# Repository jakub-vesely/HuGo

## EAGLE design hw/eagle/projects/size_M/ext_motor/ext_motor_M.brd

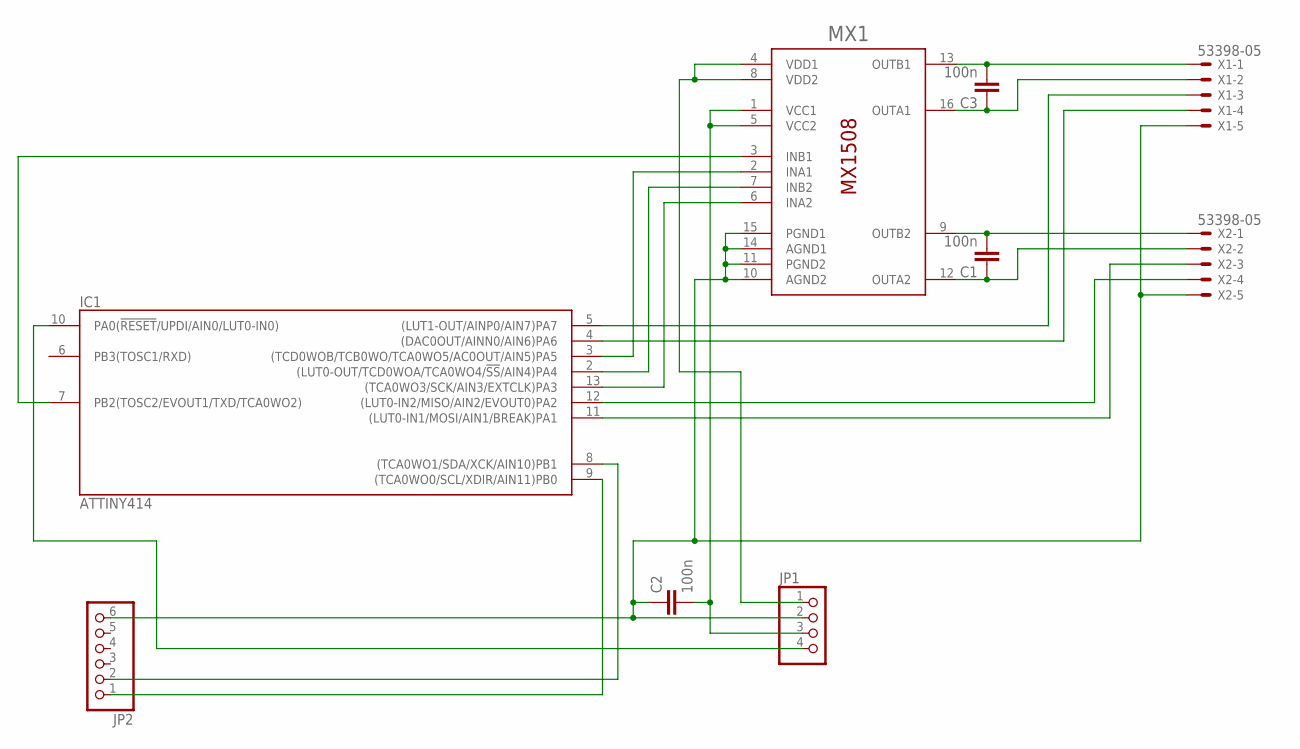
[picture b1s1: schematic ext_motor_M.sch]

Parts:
C1, C2, C3: 100n; C0805K
IC1: ATTINY414; SO14
JP1: PINHD-1X4; 1X04
JP2: PINHD-1X6; 1X06
MX1: MX1508; SOP16
X1, X2: 53398-05

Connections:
FOTO1: IC1.5 ((LUT1-OUT/AINP0/AIN7)PA7), X1.3
FOTO2: IC1.12 ((LUT0-IN2/MISO/AIN2/EVOUT0)PA2), X2.4
GND: C2.1, IC1.14 (GND), JP1.2, JP2.6, MX1.10 (AGND2), MX1.11 (PGND2), MX1.14 (AGND1), MX1.15 (PGND1), X1.5, X2.5
INA1: IC1.3 ((TCD0WOB/TCB0WO/TCA0WO5/AC0OUT/AIN5)PA5), MX1.2 (INA1)
INA2: IC1.13 ((TCA0WO3/SCK/AIN3/EXTCLK)PA3), MX1.6 (INA2)
INB1: IC1.7 (PB2(TOSC2/EVOUT1/TXD/TCA0WO2)), MX1.3 (INB1)
INB2: IC1.2 ((LUT0-OUT/TCD0WOA/TCA0WO4/!SS!/AIN4)PA4), MX1.7 (INB2)
LED1: IC1.4 ((DAC0OUT/AINN0/AIN6)PA6), X1.4
LED2: IC1.11 ((LUT0-IN1/MOSI/AIN1/BREAK)PA1), X2.3
M1: C3.2, MX1.13 (OUTB1), X1.1
M2: C3.1, MX1.16 (OUTA1), X1.2
M3: C1.2, MX1.9 (OUTB2), X2.1
M4: C1.1, MX1.12 (OUTA2), X2.2
M_SRC: JP1.1, MX1.4 (VDD1), MX1.8 (VDD2)
unnamed: IC1.10 (PA0(!RESET!/UPDI/AIN0/LUT0-IN0)), JP1.4
unnamed: IC1.9 ((TCA0WO0/SCL/XDIR/AIN11)PB0), JP2.1
unnamed: IC1.8 ((TCA0WO1/SDA/XCK/AIN10)PB1), JP2.2
VCC: C2.2, IC1.1 (VCC), JP1.3, MX1.1 (VCC1), MX1.5 (VCC2)

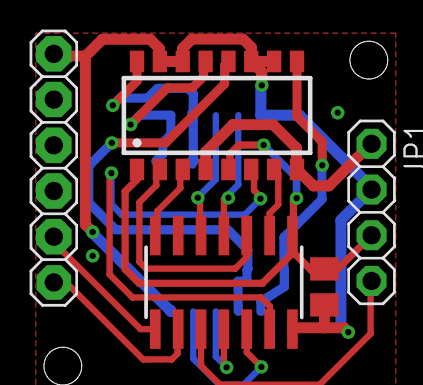
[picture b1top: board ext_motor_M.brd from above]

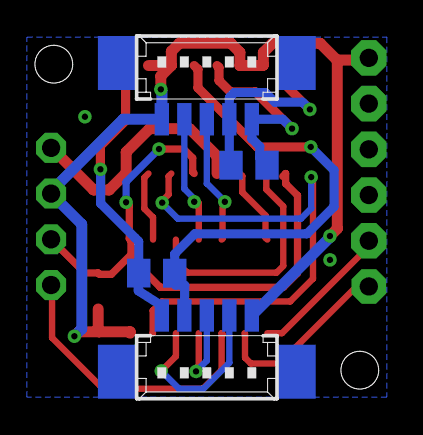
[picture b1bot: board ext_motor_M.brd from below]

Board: 2 copper layers, 9 parts (4 on the bottom side), 18 nets.

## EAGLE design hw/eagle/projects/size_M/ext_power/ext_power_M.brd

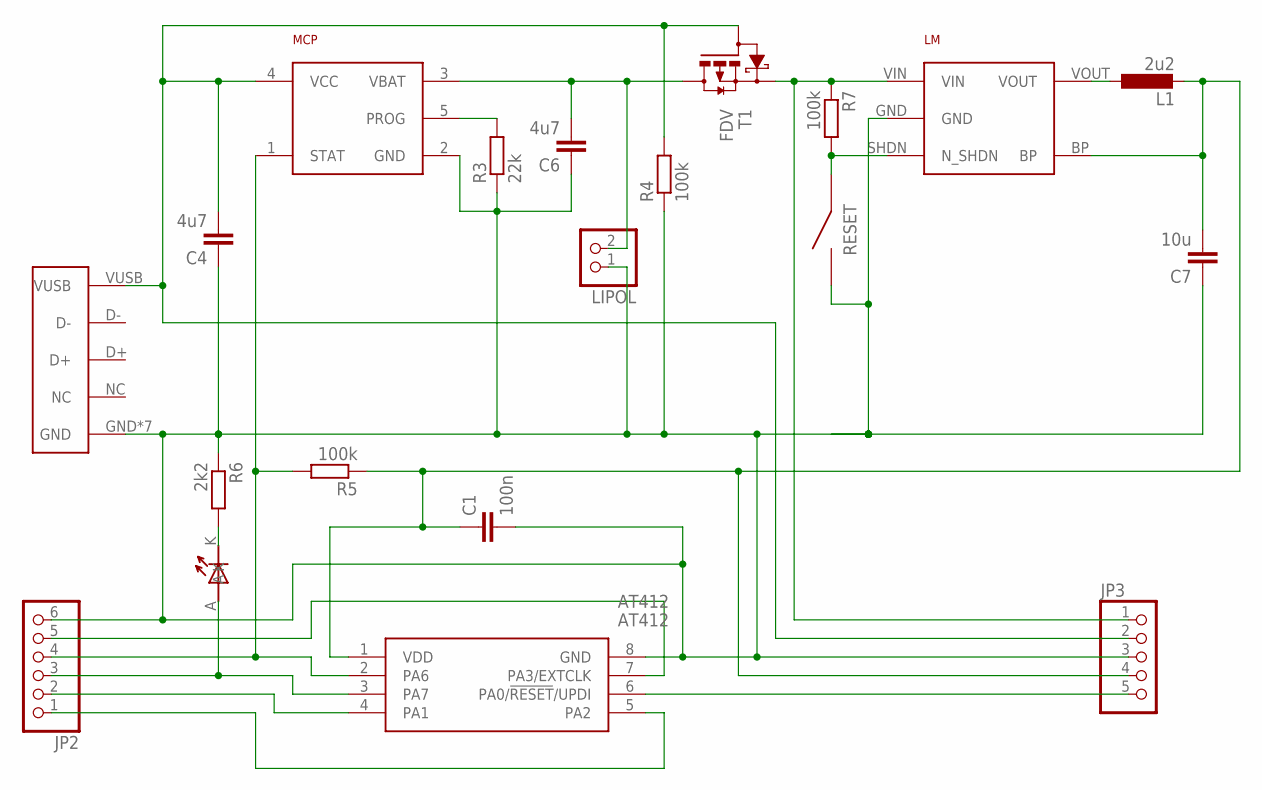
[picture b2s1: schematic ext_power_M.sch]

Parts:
AT412: AT412; SOIC127P600X175-8N
C1: 100n; C0603
C4, C6: 4u7; C0603
C7: 10u; C0603
D1: LED1.8
JP2: PINHD-1X6; 1X06
JP3: PINHD-1X5; 1X05
L1: 2u2; L3230M
LIPOL: PINHD-1X2; 1X02
LM: TC; SOT32-5
MCP: MCP; SOT23-5
R3: 22k; R0603
R4, R5, R7: 100k; R0603
R6: 2k2; R0603
RESET: BYTTON-B3U; BUTTON-B3U
T1: FDV; SOT23
USB: MICRO-USB

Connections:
GND: AT412.8 (GND), C1.2, C4.1, C6.1, C7.1, JP2.6, JP3.3, LIPOL.1, LM.GND, MCP.2 (GND), R3.1, R4.1, R6.1, RESET.P$2, USB.GND, USB.GND1 (GND), USB.GND2 (GND), USB.GND3 (GND), USB.GND4 (GND), USB.P$1 (GND), USB.P$2 (GND)
unnamed: L1.1, LM.VOUT
unnamed: C6.2, LIPOL.2, MCP.3 (VBAT), T1.D
unnamed: C4.2, JP3.2, MCP.4 (VCC), R4.2, T1.G, USB.VUSB
unnamed: MCP.5 (PROG), R3.2
unnamed: JP3.1, LM.VIN, R7.1, T1.S
unnamed: D1.K, R6.2
unnamed: LM.SHDN (N_SHDN), R7.2, RESET.P$1
PA3: AT412.7 (PA3/EXTCLK), JP2.5
PA6: AT412.2 (PA6), JP2.4, MCP.1 (STAT), R5.2
PA7: AT412.3 (PA7), D1.A, JP2.3
SCL: AT412.5 (PA2), JP2.1
SDA: AT412.4 (PA1), JP2.2
UPDI: AT412.6 (PA0/!RESET!/UPDI), JP3.5
VDD: AT412.1 (VDD), C1.1, C7.2, JP3.4, L1.2, LM.BP, R5.1

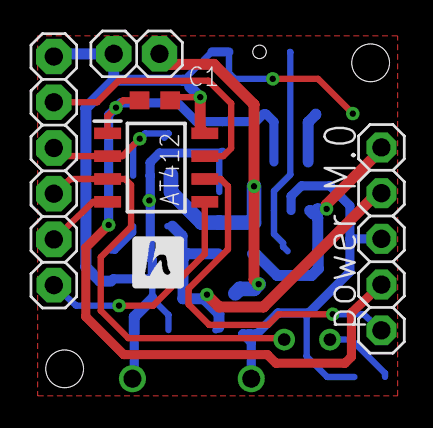
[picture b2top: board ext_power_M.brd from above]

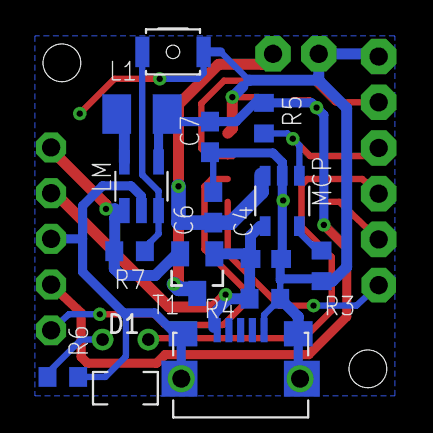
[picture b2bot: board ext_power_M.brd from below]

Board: 2 copper layers, 20 parts (15 on the bottom side), 15 nets.

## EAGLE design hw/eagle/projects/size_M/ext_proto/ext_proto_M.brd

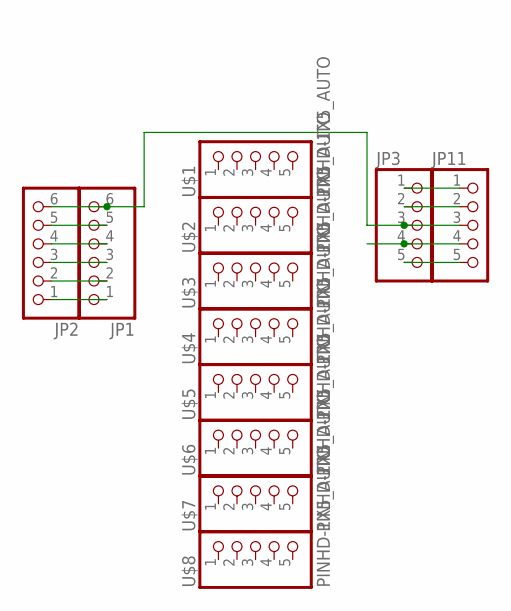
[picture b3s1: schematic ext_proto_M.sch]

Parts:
JP1, JP2: PINHD-1X6; 1X06
JP3, JP11: PINHD-1X5; 1X05
U$1, U$2, U$3, U$4, U$5, U$6, U$7, U$8: PINHD-1X5_AUTO; 1X5_AUTO

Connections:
GND: JP1.6, JP2.6, JP3.3, JP11.3
unnamed: JP1.5, JP2.5
unnamed: JP1.4, JP2.4
unnamed: JP1.3, JP2.3
unnamed: JP1.2, JP2.2
unnamed: JP1.1, JP2.1
unnamed: JP3.5, JP11.5
unnamed: JP3.2, JP11.2
unnamed: JP3.1, JP11.1
VDD: JP3.4, JP11.4

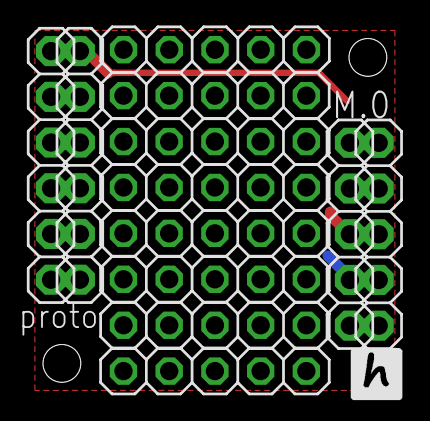
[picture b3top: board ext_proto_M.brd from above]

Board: 2 copper layers, 12 parts (0 on the bottom side), 10 nets.

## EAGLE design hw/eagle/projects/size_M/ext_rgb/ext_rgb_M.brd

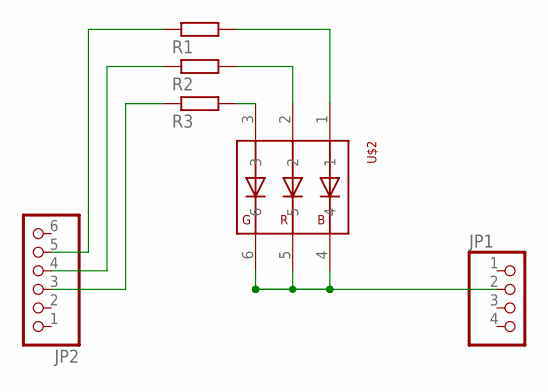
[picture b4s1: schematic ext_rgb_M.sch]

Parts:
JP1: PINHD-1X4; 1X04
JP2: PINHD-1X6; 1X06
R1, R2, R3: R-EU_R0603; R0603
U$2: RGB_WW-FCE50TC-Q1

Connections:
GND: JP1.2, U$2.4, U$2.5, U$2.6
unnamed: R1.2, U$2.1
unnamed: R3.2, U$2.3
unnamed: R2.2, U$2.2
unnamed: JP2.5, R1.1
unnamed: JP2.4, R2.1
unnamed: JP2.3, R3.1

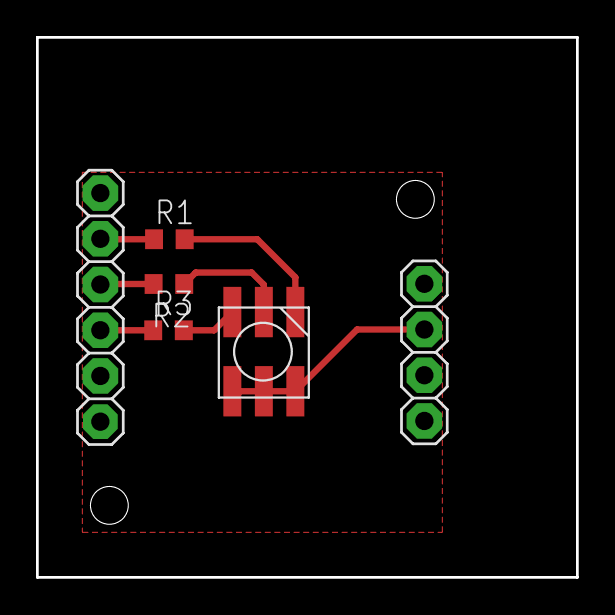
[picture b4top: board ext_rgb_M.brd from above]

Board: 2 copper layers, 30.0 x 30.0 mm, 6 parts (0 on the bottom side), 7 nets.

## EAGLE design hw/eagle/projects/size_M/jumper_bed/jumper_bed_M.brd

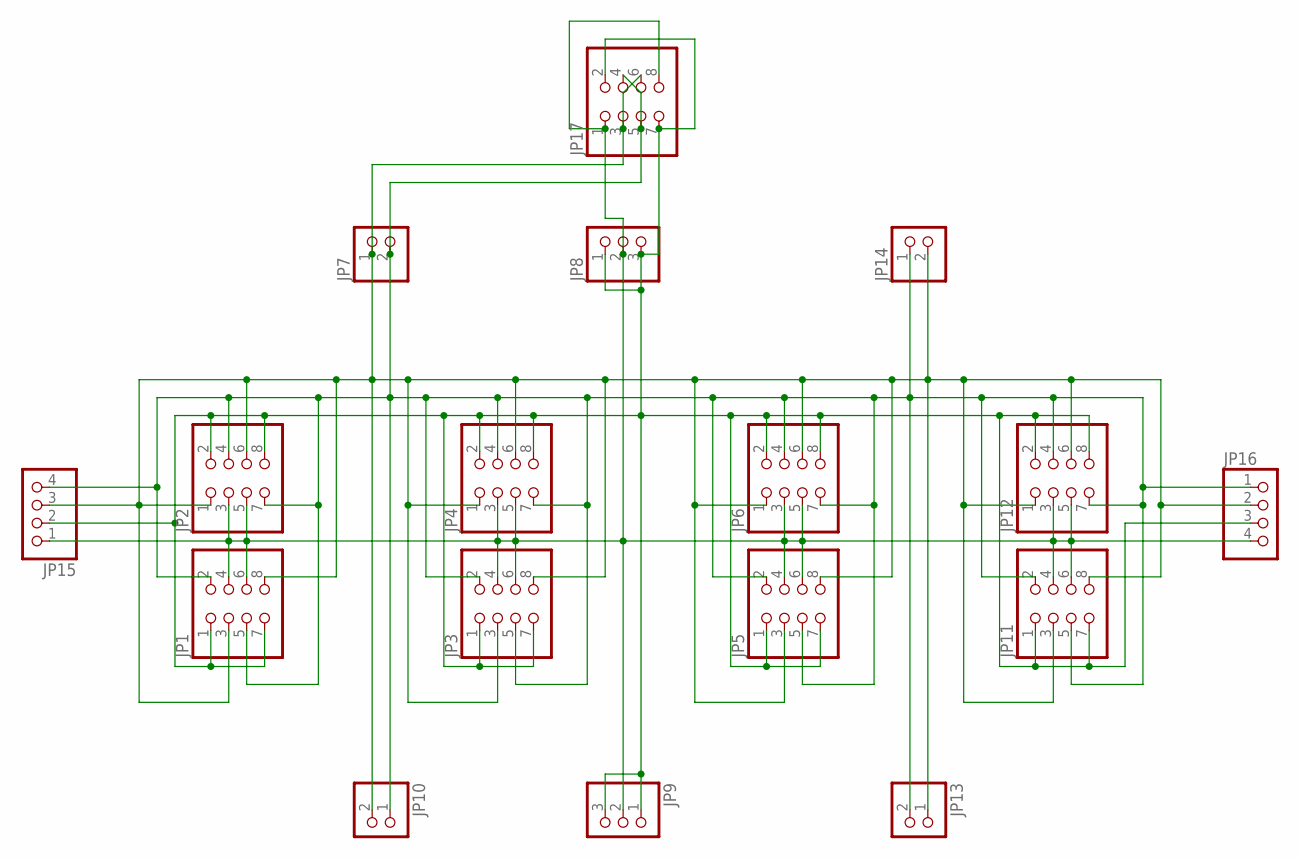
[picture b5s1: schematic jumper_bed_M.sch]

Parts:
JP1, JP2, JP3, JP4, JP5, JP6, JP11, JP12: PINHD-2X4; 2X04
JP7, JP14: PINHD-1X2/90; 1X02/90
JP8: PINHD-1X3/90; 1X03/90
JP9: PINHD-1X31X03/90F; 1X03/90F
JP10, JP13: PINHD-1X21X02/90F; 1X02/90F
JP15, JP16: PINHD-1X4; 1X04
JP17: PINHD-2X4/90; 2X04/90

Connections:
GND: JP1.1, JP1.7, JP2.2, JP2.8, JP3.1, JP3.7, JP4.2, JP4.8, JP5.1, JP5.7, JP6.2, JP6.8, JP8.1, JP8.3, JP9.1, JP9.3, JP11.1, JP11.7, JP12.2, JP12.8, JP15.2, JP16.3, JP17.2, JP17.7
SCL: JP1.2, JP1.5, JP2.4, JP2.7, JP3.2, JP3.5, JP4.4, JP4.7, JP5.2, JP5.5, JP6.4, JP6.7, JP7.2, JP10.1, JP11.2, JP11.5, JP12.4, JP12.7, JP13.2, JP14.1, JP15.4, JP16.1, JP17.4, JP17.5
SDA: JP1.3, JP1.8, JP2.1, JP2.6, JP3.3, JP3.8, JP4.1, JP4.6, JP5.3, JP5.8, JP6.1, JP6.6, JP7.1, JP10.2, JP11.3, JP11.8, JP12.1, JP12.6, JP13.1, JP14.2, JP15.3, JP16.2, JP17.3, JP17.6
VCC: JP1.4, JP1.6, JP2.3, JP2.5, JP3.4, JP3.6, JP4.3, JP4.5, JP5.4, JP5.6, JP6.3, JP6.5, JP8.2, JP9.2, JP11.4, JP11.6, JP12.3, JP12.5, JP15.1, JP16.4, JP17.1, JP17.8

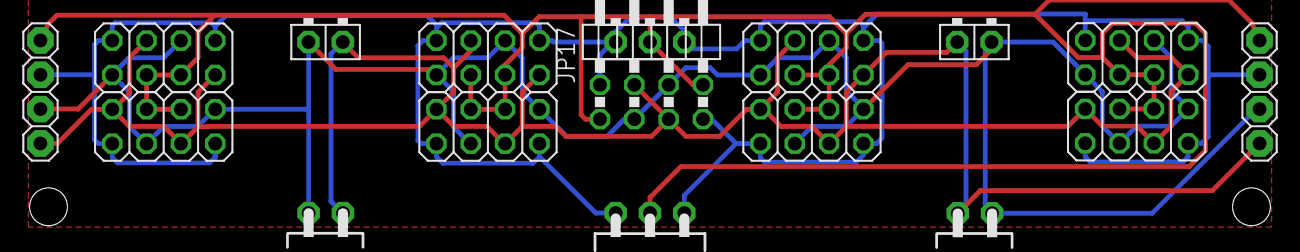
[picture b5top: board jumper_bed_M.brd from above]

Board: 2 copper layers, 17 parts (0 on the bottom side), 4 nets.

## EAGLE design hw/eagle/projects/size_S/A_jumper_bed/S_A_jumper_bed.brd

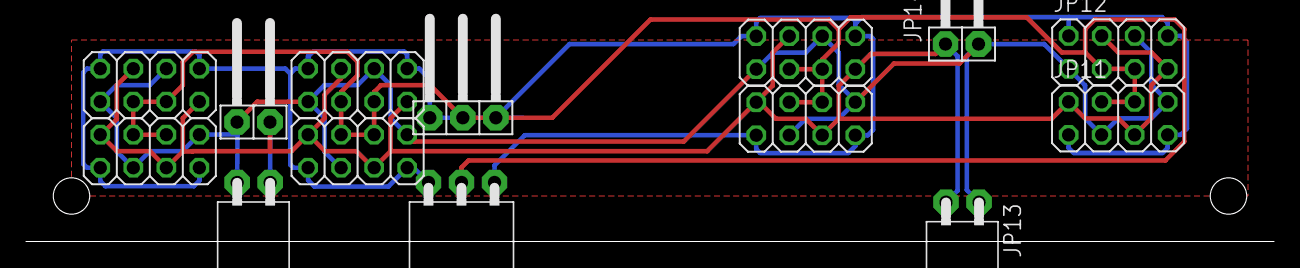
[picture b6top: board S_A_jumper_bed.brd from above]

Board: 2 copper layers, 14 parts (0 on the bottom side), 4 nets.

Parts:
JP1, JP2, JP3, JP4, JP5, JP6, JP11, JP12: 2X04
JP7, JP14: 1X02/90
JP8: 1X03/90
JP9: 1X03/90F
JP10, JP13: 1X02/90F

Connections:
GND: JP1.1, JP1.7, JP2.2, JP2.8, JP3.1, JP3.7, JP4.2, JP4.8, JP5.1, JP5.7, JP6.2, JP6.8, JP8.1, JP8.3, JP9.1, JP9.3, JP11.1, JP11.7, JP12.2, JP12.8
SCL: JP1.2, JP1.5, JP2.4, JP2.7, JP3.2, JP3.5, JP4.4, JP4.7, JP5.2, JP5.5, JP6.4, JP6.7, JP7.2, JP10.1, JP11.2, JP11.5, JP12.4, JP12.7, JP13.2, JP14.1
SDA: JP1.3, JP1.8, JP2.1, JP2.6, JP3.3, JP3.8, JP4.1, JP4.6, JP5.3, JP5.8, JP6.1, JP6.6, JP7.1, JP10.2, JP11.3, JP11.8, JP12.1, JP12.6, JP13.1, JP14.2
VCC: JP1.4, JP1.6, JP2.3, JP2.5, JP3.4, JP3.6, JP4.3, JP4.5, JP5.4, JP5.6, JP6.3, JP6.5, JP8.2, JP9.2, JP11.4, JP11.6, JP12.3, JP12.5

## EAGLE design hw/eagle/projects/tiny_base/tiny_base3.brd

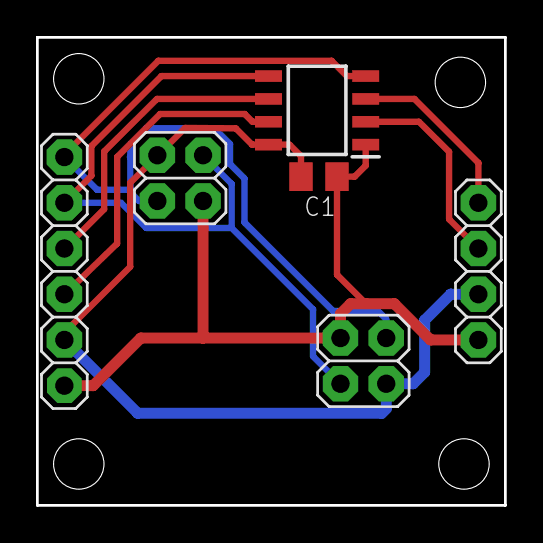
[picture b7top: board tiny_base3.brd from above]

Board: 2 copper layers, 26.0 x 26.0 mm, 6 parts (0 on the bottom side), 8 nets.

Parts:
C1: C0805K
IC1: ATTINY412-SSN; SOIC127P600X175-8N
JP1: 1X04
JP2: 1X06
JP3, JP4: 2X02

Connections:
GND: C1.2, IC1.8, JP1.3, JP2.2, JP3.4, JP4.1
P0: IC1.2, JP1.2
P1: IC1.3, JP1.1
P4: IC1.7, JP2.3
SCL: IC1.5, JP2.5, JP3.3, JP4.2
SDA: IC1.4, JP2.6, JP3.2, JP4.3
UPDI: IC1.6, JP2.4
VDD: C1.1, IC1.1, JP1.4, JP2.1, JP3.1, JP4.4
